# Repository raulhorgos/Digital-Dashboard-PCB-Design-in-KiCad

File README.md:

# Digital Dashboard PCB Design in KiCad 

-Designed a 2-layer microcontroller-based dashboard system using a custom
microcontroller and a LCD interface.

-Integrated analog and digital inputs for automotive monitoring, including RPM, Speed,
Fuel Level, and Oil/Coolant Temperature sensors.

-Created custom schematic symbols and IPC-compliant footprints for components such
as SO-28, SOT-223, and TO-220 packages.

-Managed power distribution using LM7805 and LM317 voltage regulators, adhering to
strict track width requirements (0.6mm for power, 0.25mm for signals).

-Executed the full PCB design flow from schematic capture to Gerber generation for a
mixed-signal dashboard using KiCad.

Finalized manufacturing outputs including Drill files, Assembly drawings, and 3D model
integration.

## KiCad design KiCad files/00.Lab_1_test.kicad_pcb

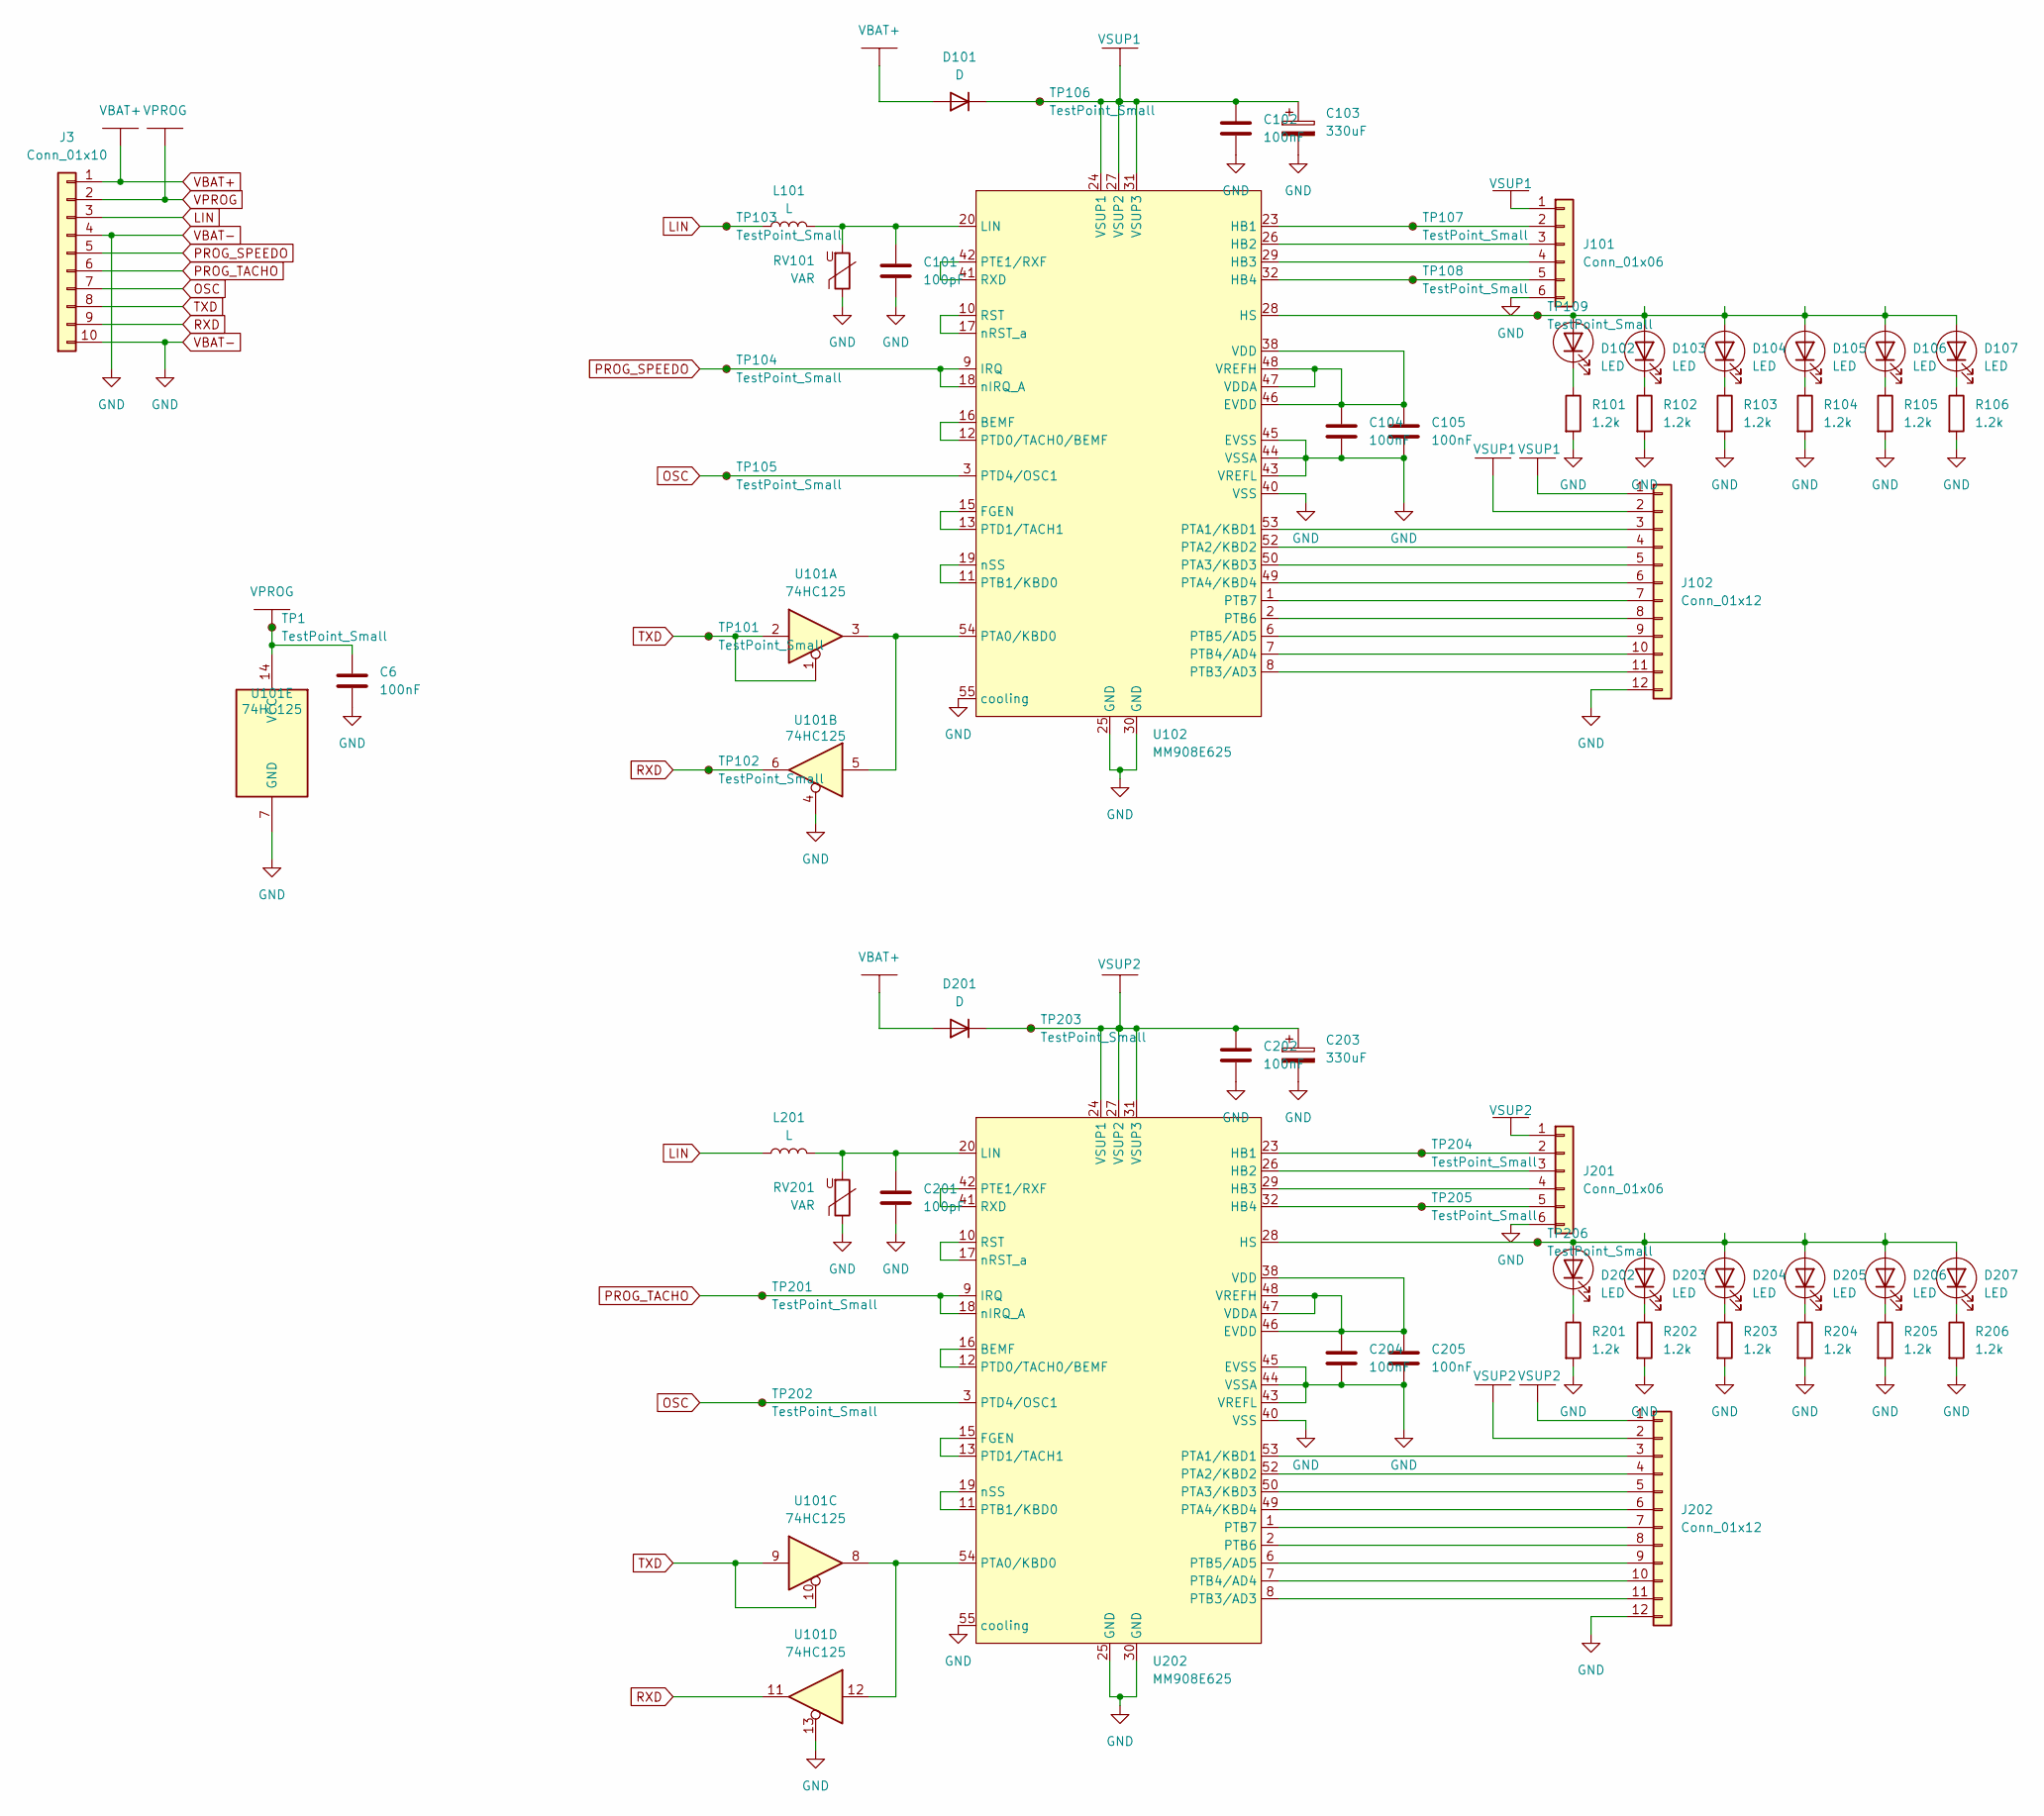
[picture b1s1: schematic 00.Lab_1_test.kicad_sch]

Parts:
C6, C102, C104, C105, C202, C204, C205: 100nF; C_100nF
C101, C201: 100pF; C_100pF
C103, C203: 330uF; CP_330uF_D
D101, D201: D; D_403
D102, D103, D104, D105, D106, D107, D202, D203, D204, D205, D206, D207: LED; LED_1206_Metric
J3: Conn_01x10; PinSocket_1x20_nou
J101, J201: Conn_01x06; PinSocket_1x06_P2.54mm_Vertical
J102, J202: Conn_01x12; PinHeader_1x12_P2.54mm
L101, L201: L; L_0805_Metric
R101, R102, R103, R104, R105, R106, R201, R202, R203, R204, R205, R206: 1.2k; R_0402
RV101, RV201: VAR
TP1, TP101, TP102, TP103, TP104, TP105, TP106, TP107, TP108, TP109, TP201, TP202, TP203, TP204, TP205, TP206: TestPoint_Small; TestPoint_Pad
U101: 74HC125; SOIC-14 U3
U102, U202: MM908E625; SOIC-54, var 2

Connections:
LIN: J3.3, L101.1, L201.1, TP103.1
unnamed: D102.2 (A), D103.2 (A), D104.2 (A), D105.2 (A), D106.2 (A), D107.2 (A), TP109.1, U102.28 (HS)
unnamed: D102.1 (K), R101.1
unnamed: D103.1 (K), R102.1
unnamed: D104.1 (K), R103.1
unnamed: D105.1 (K), R104.1
unnamed: D106.1 (K), R105.1
unnamed: D107.1 (K), R106.1
unnamed: D202.2 (A), D203.2 (A), D204.2 (A), D205.2 (A), D206.2 (A), D207.2 (A), TP206.1, U202.28 (HS)
unnamed: D202.1 (K), R201.1
unnamed: D203.1 (K), R202.1
unnamed: D204.1 (K), R203.1
unnamed: D205.1 (K), R204.1
unnamed: D206.1 (K), R205.1
unnamed: D207.1 (K), R206.1
unnamed: J101.2, TP107.1, U102.23 (HB1)
unnamed: J101.3, U102.26 (HB2)
unnamed: J101.4, U102.29 (HB3)
unnamed: J101.5, TP108.1, U102.32 (HB4)
unnamed: J102.3, U102.53 (PTA1/KBD1)
unnamed: J102.4, U102.52 (PTA2/KBD2)
unnamed: J102.5, U102.50 (PTA3/KBD3)
unnamed: J102.6, U102.49 (PTA4/KBD4)
unnamed: J102.7, U102.1 (PTB7)
unnamed: J102.8, U102.2 (PTB6)
unnamed: J102.9, U102.6 (PTB5/AD5)
unnamed: J102.10, U102.7 (PTB4/AD4)
unnamed: J102.11, U102.8 (PTB3/AD3)
unnamed: J201.2, TP204.1, U202.23 (HB1)
unnamed: J201.3, U202.26 (HB2)
unnamed: J201.4, U202.29 (HB3)
unnamed: J201.5, TP205.1, U202.32 (HB4)
unnamed: J202.3, U202.53 (PTA1/KBD1)
unnamed: J202.4, U202.52 (PTA2/KBD2)
unnamed: J202.5, U202.50 (PTA3/KBD3)
unnamed: J202.6, U202.49 (PTA4/KBD4)
unnamed: J202.7, U202.1 (PTB7)
unnamed: J202.8, U202.2 (PTB6)
unnamed: J202.9, U202.6 (PTB5/AD5)
unnamed: J202.10, U202.7 (PTB4/AD4)
unnamed: J202.11, U202.8 (PTB3/AD3)
unnamed: U102.12 (PTD0/TACH0/BEMF), U102.16 (BEMF)
unnamed: C104.1, C105.1, U102.38 (VDD), U102.46 (EVDD), U102.47 (VDDA), U102.48 (VREFH)
unnamed: U102.13 (PTD1/TACH1), U102.15 (FGEN)
unnamed: C101.1, L101.2, RV101.2, U102.20 (LIN)
unnamed: U101.3, U101.5, U102.54 (PTA0/KBD0)
unnamed: U102.11 (PTB1/KBD0), U102.19 (nSS)
unnamed: U102.41 (RXD), U102.42 (PTE1/RXF)
unnamed: U102.10 (RST), U102.17 (nRST_a)
unnamed: U202.12 (PTD0/TACH0/BEMF), U202.16 (BEMF)
unnamed: C204.1, C205.1, U202.38 (VDD), U202.46 (EVDD), U202.47 (VDDA), U202.48 (VREFH)
unnamed: U202.13 (PTD1/TACH1), U202.15 (FGEN)
unnamed: C201.1, L201.2, RV201.2, U202.20 (LIN)
unnamed: U101.8, U101.12, U202.54 (PTA0/KBD0)
unnamed: U202.11 (PTB1/KBD0), U202.19 (nSS)
unnamed: U202.41 (RXD), U202.42 (PTE1/RXF)
unnamed: U202.10 (RST), U202.17 (nRST_a)
OSC: J3.7, TP105.1, TP202.1, U102.3 (PTD4/OSC1), U202.3 (PTD4/OSC1)
PROG_SPEEDO: J3.5, TP104.1, U102.9 (IRQ), U102.18 (nIRQ_A)
PROG_TACHO: J3.6, TP201.1, U202.9 (IRQ), U202.18 (nIRQ_A)
RXD: J3.9, TP102.1, U101.6, U101.11
TXD: J3.8, TP101.1, U101.1, U101.2, U101.9, U101.10
VBAT+: D101.2 (A), D201.2 (A), J3.1
VBAT-: C6.2, C101.2, C102.2, C103.2, C104.2, C105.2, C201.2, C202.2, C203.2, C204.2, C205.2, J3.4, J3.10, J101.6, J102.12, J201.6, J202.12, R101.2, R102.2, R103.2, R104.2, R105.2, R106.2, R201.2, R202.2, R203.2, R204.2, R205.2, R206.2, RV101.1, RV201.1, U101.4, U101.7 (GND), U101.13, U102.25 (GND), U102.30 (GND), U102.40 (VSS), U102.43 (VREFL), U102.44 (VSSA), U102.45 (EVSS), U102.55 (cooling), U202.25 (GND), U202.30 (GND), U202.40 (VSS), U202.43 (VREFL), U202.44 (VSSA), U202.45 (EVSS), U202.55 (cooling)
VPROG: C6.1, J3.2, TP1.1, U101.14 (VCC)
VSUP1: C102.1, C103.1, D101.1 (K), J101.1, J102.1, J102.2, TP106.1, U102.24 (VSUP1), U102.27 (VSUP2), U102.31 (VSUP3)
VSUP2: C202.1, C203.1, D201.1 (K), J201.1, J202.1, J202.2, TP203.1, U202.24 (VSUP1), U202.27 (VSUP2), U202.31 (VSUP3)

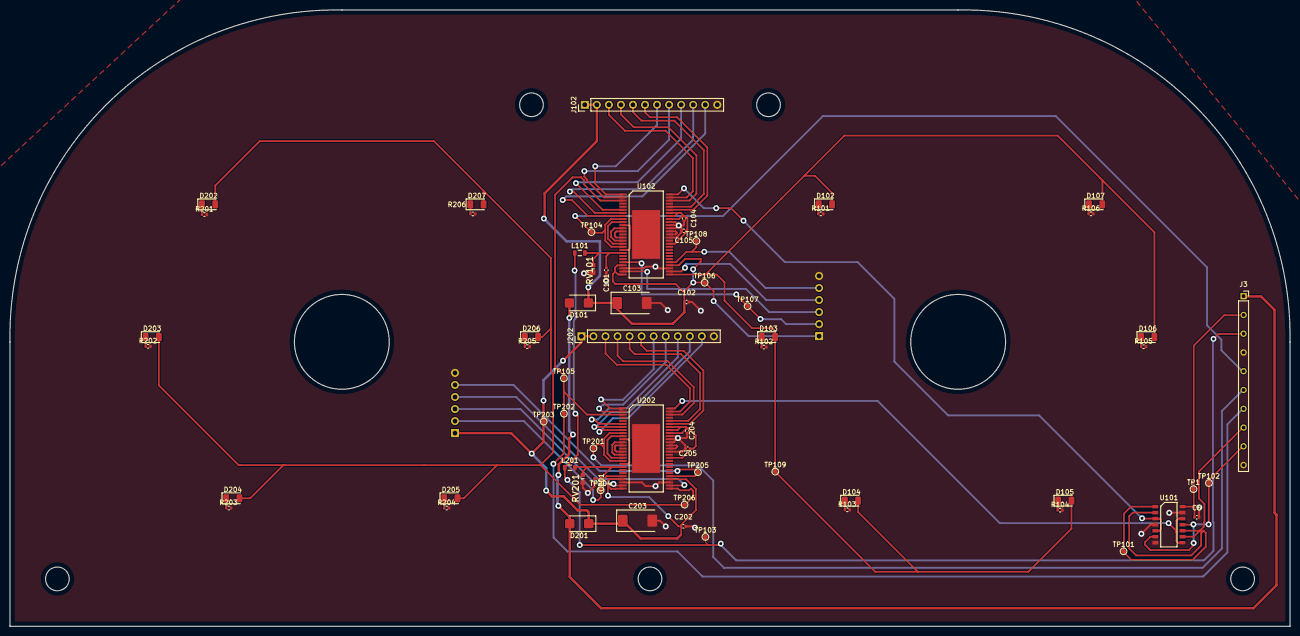
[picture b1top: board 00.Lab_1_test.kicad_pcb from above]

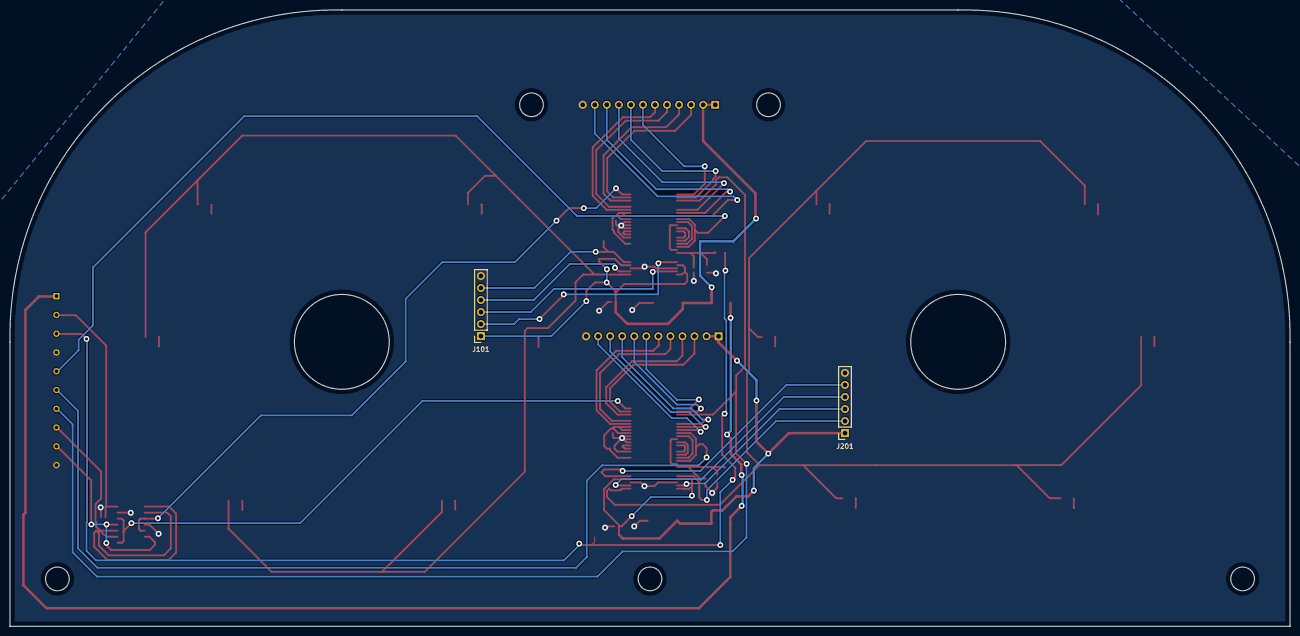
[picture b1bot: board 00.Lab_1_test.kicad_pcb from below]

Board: 2 copper layers, 270.0 x 130.0 mm, 65 parts (2 on the bottom side), 67 nets.
